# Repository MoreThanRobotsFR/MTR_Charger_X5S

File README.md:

<!-- markdownlint-configure-file { "MD004": { "style": "consistent" } } -->
<!-- markdownlint-disable MD033 -->
<p align="center">
    
    <br>
    <strong>Coding, Hardware and fun !</strong>
</p>
<!-- markdownlint-enable MD033 -->

<body style="background-color:#FFBF00;">
</body>

# MoreThanRobots
* Check the [YOUTUBE-EN-FR](https://www.youtube.com/@morethanrobots) channel.

# Coding
* C/C++
* Python
* MicroPython
* CircuitPython 

# Hardward
* Arduino Uno / Mega / Nano
* Raspberry Pi / Pico / RP2040
* NodeMCU ESP8266 / ESP32

# Schematic
* Kicad
* Altium designer

# Last Project
* [MTR Reflow Plate](https://github.com/MoreThanRobotsFR/MTR_Reflow_Plate)
* [MTR Tiny MD](https://github.com/MoreThanRobotsFR/MTR_Tiny_MD)
* [MTR Multisensor](https://github.com/MoreThanRobotsFR/MTR_C3_TempHum)

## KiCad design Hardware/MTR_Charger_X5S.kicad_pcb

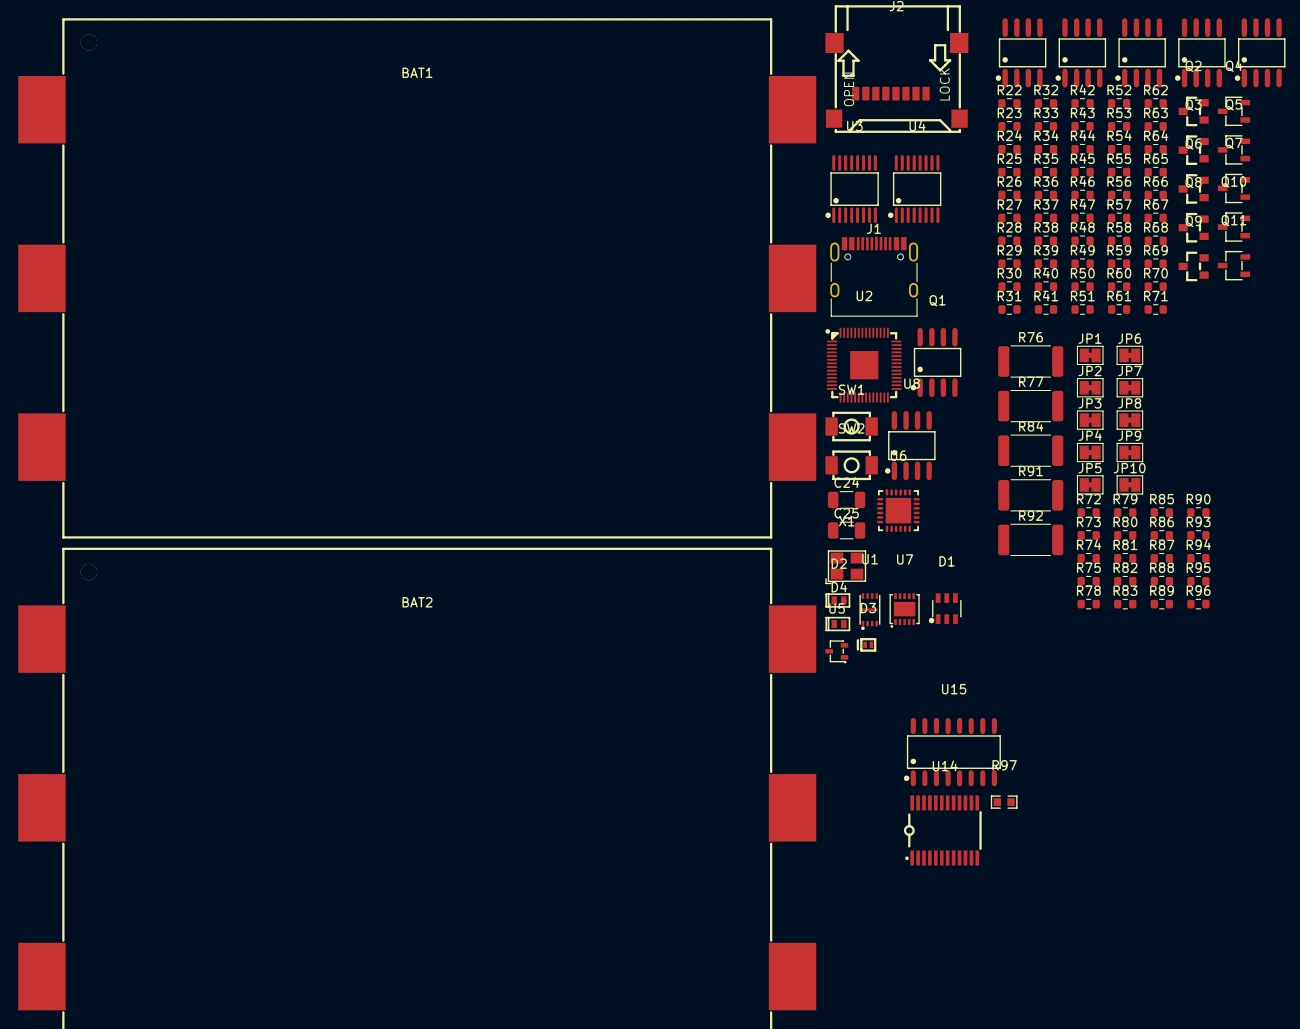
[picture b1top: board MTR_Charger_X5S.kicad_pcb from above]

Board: 2 copper layers, 125 parts (0 on the bottom side), 118 nets, no tracks yet.

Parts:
BAT1, BAT2: BH-18650-B5BA016; BAT-SMD_BH-18650-B5BA016
C24, C25: 1uF; C_1206_3216Metric
D1: USBLC6-2SC6; SOT-23-6_L2.9-W1.6-P0.95-LS2.8-BL
D2, D4: ESDA25P35; DFN1610-2_L1.6-W1.0-P1.05-RD
D3: D_Schottky_Small; X2-DFN1006-2_L1.0-W0.6-P0.65-RD
J1: Korean Hroparts Elec TYPE-C-31-M-12; USB_C_Receptacle_HRO_TYPE-C-31-M-12
J2: Micro_SD_Card; TF-SMD_TF-04A
JP1, JP2, JP3, JP4, JP5, JP6, JP7, JP8, JP9, JP10: SolderJumper_2_Bridged; SolderJumper-2_P1.3mm_Bridged_Pad1.0x1.5mm
Q1: IRF7324TRPBF; SOIC-8_L4.9-W3.9-P1.27-LS6.0-BL
Q2, Q3, Q6, Q8, Q9: AO3401A; SOT-23_L2.9-W1.3-P1.90-LS2.4-BR
Q4, Q5, Q7, Q10, Q11: AO3480C; SOT-23-3_L2.9-W1.6-P1.90-LS2.8-BR
R22, R23, R24, R25, R26, R27, R28, R29, R30, R31, R32, R33, R34, R35, R36, R37, R38, R39, R40, R41, R42, R43, R44, R45, R46, R47, R48, R49, R50, R51, R52, R53, R54, R55, R56, R57, R58, R59, R60, R61, R62, R63, R64, R65, R66, R67, R68, R69, R70, R71, R72, R73, R80, R81, R82, R86, R87, R88, R95, R96: 100k; R_0603_1608Metric
R74, R75, R78, R79, R83, R85, R89, R90, R93, R94: 1k; R_0603_1608Metric
R76, R77, R84, R91, R92: 33m; R_2512_6332Metric
R97: NCP18XH103F03RB; R0603
SW1: Boot; SW-SMD_L4.0-W3.0-LS5.0
SW2: Reset; SW-SMD_L4.0-W3.0-LS5.0
U1: W25Q16JVUXIQ; USON-8_L3.0-W2.0-P0.50-BL-EP
U2: RP2040; LQFN-56_L7.0-W7.0-P0.4-EP
U3, U4: ADS7830IPWR; TSSOP-16_L5.0-W4.4-P0.65-LS6.4-BL
U5: ESDA25W; SOT-323-3_L2.1-W1.3-P1.32-LS2.1-BR
U6: STUSB4500QTR; QFN-24_L4.0-W4.0-P0.50-BL-EP2.8
U7: MCP73833-AMI/MF; DFN-10_L3.0-W3.0-P0.50-BL-EP-1
U8: LMV358IDR; SOIC-8_L4.9-W3.9-P1.27-LS6.0-BL
U9, U10, U11, U12, U13: LMC6482AIMX/NOPB; SOIC-8_L4.9-W3.9-P1.27-LS6.0-BL
U14: TCA9535PWR_C130204; TSSOP-24_L7.8-W4.4-P0.65-LS6.4-BL
U15: CD74HCT4051M96; SOP-16_L10.0-W3.9-P1.27-LS6.0-BL
X1: X322512MSB4SI; OSC-SMD_4P-L3.2-W2.5-BL

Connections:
+1V1: U2.23 (DVDD), U2.45 (VREG_VOUT), U2.50 (DVDD)
+3.3V: U1.8 (VCC), U2.1 (IOVDD), U2.10 (IOVDD), U2.22 (IOVDD), U2.33 (IOVDD), U2.42 (IOVDD), U2.43 (ADC_AVDD), U2.44 (VREG_IN), U2.48 (USB_VDD), U2.49 (IOVDD), U3.16 (+VDD), U4.16 (+VDD), U15.16 (VCC)
+5V: U9.8 (VCC+), U10.8 (VCC+), U11.8 (VCC+), U12.8 (VCC+), U13.8 (VCC+)
/Batteries current sensing/sence_01+: JP1.1 (A), R74.1, R76.1
/Batteries current sensing/sence_01-: JP3.1 (A), R76.2, R78.1
/Batteries current sensing/sence_02+: JP2.1 (A), R75.1, R77.1
/Batteries current sensing/sence_02-: JP4.1 (A), R77.2, R79.1
/Batteries current sensing/sence_03+: JP5.1 (A), R83.1, R84.1
/Batteries current sensing/sence_03-: JP6.1 (A), R84.2, R85.1
/Batteries current sensing/sence_04+: JP7.1 (A), R89.1, R91.1
/Batteries current sensing/sence_04-: JP9.1 (A), R91.2, R93.1
/Batteries current sensing/sence_05+: JP8.1 (A), R90.1, R92.1
/Batteries current sensing/sence_05-: JP10.1 (A), R92.2, R94.1
/CC1: J1.A5 (CC1), U5.1 (K), U6.1 (CC1DB), U6.2 (CC1)
/CC2: J1.B5 (CC2), U5.2 (K), U6.4 (CC2), U6.5 (CC2DB)
/D+: D1.3 (L2), J1.A6 (D+), J1.B6 (D+)
/D-: D1.1 (L1), J1.A7 (D-), J1.B7 (D-)
/Mux_CELL_01_S0: U14.9 (P05), U15.11 (S0)
/Mux_CELL_01_S1: U14.8 (P04), U15.10 (S1)
/Mux_CELL_01_S2: U14.7 (P03), U15.9 (S2)
/PG_Cell_01: U7.7 (~PG), U14.4 (P00)
/PROG_CELL_01: U7.6 (PROG), U15.3 (A)
/STAT1_Cell_01: U7.3 (STAT1), U14.6 (P02)
/STAT2_Cell_01: U7.4 (STAT2), U14.5 (P01)
/XIN: U2.20 (XIN), X1.3
/XOUT: U2.21 (XOUT), X1.1
ALERT: U2.8 (GPIO6), U6.19 (ALERT)
CELL_01+: BAT1.2, JP3.2 (B), Q2.2 (S), R27.2
CELL_02+: BAT1.4, JP4.2 (B), Q3.2 (S), R29.2
CELL_03+: BAT1.6, JP6.2 (B), Q6.2 (S), R45.2
CELL_04+: BAT2.2, JP9.2 (B), Q9.2 (S), R60.2
CELL_05+: BAT2.4, JP10.2 (B), Q8.2 (S), R57.2
CHARGING_01: C25.1, JP1.2 (B), U7.9 (VBAT), U7.10 (VBAT)
Current_cell_01: R80.2, U4.1 (CH0), U9.1
Current_cell_02: R81.2, U4.2 (CH1), U10.1
Current_cell_03: R86.2, U4.3 (CH2), U11.1
Current_cell_04: R95.2, U4.4 (CH3), U12.1
Current_cell_05: R96.2, U4.5 (CH4), U13.1
GND: C24.2, C25.2, D1.2 (VN), D2.2 (A2), D4.2 (A2), J1.A1 (GND), J1.A12 (GND), J1.B1 (GND), J1.B12 (GND), J1.S1 (SHIELD), R22.1, R23.1, R42.1, R52.1, R54.1, R72.2, R73.2, R82.2, R87.2, R88.2, R97.1, SW1.1, SW2.1, U1.4 (GND), U2.19 (TESTEN), U2.57 (GND), U5.3 (A), U6.3 (NC), U6.10 (GND), U6.22 (VSYS), U6.25 (EP), U7.5 (VSS), U7.11 (PAD), U9.4 (GND), U10.4 (GND), U11.4 (GND), U12.4 (GND), U13.4 (GND), U14.12 (GND), U15.6 (~E), U15.7 (VEE), U15.8 (GND), X1.2, X1.4
unnamed: D1.5 (VP), D2.1 (A1), D3.2 (A), J1.A4 (VBUS), J1.A9 (VBUS), J1.B4 (VBUS), J1.B9 (VBUS), Q1.7 (D1), Q1.8 (D1)
unnamed: Q1.2 (G1), Q1.4 (G2)
unnamed: Q1.1 (S1), Q1.3 (S2), U6.24 (VDD)
unnamed: Q2.3 (D), R38.2
unnamed: Q2.1 (G), Q4.3 (D), R27.1
unnamed: Q3.3 (D), R39.2
unnamed: Q3.1 (G), Q5.3 (D), R29.1
unnamed: Q4.2 (S), R40.1
unnamed: Q5.2 (S), R41.1
unnamed: Q6.3 (D), R50.2
unnamed: Q6.1 (G), Q7.3 (D), R45.1
unnamed: Q7.2 (S), R51.1
unnamed: Q8.3 (D), R67.2
unnamed: Q9.3 (D), R69.2
unnamed: Q8.1 (G), Q10.3 (D), R57.1
unnamed: Q10.2 (S), R70.1
unnamed: Q9.1 (G), Q11.3 (D), R60.1
unnamed: Q11.2 (S), R71.1
unnamed: R22.2, R24.1
unnamed: R23.2, R25.1
unnamed: R24.2, R26.2
unnamed: R25.2, R28.2
unnamed: R26.1, R30.1
unnamed: R28.1, R31.1
unnamed: R30.2, R32.1
unnamed: R31.2, R33.1
unnamed: R32.2, R34.2
unnamed: R33.2, R35.2
unnamed: R34.1, R36.1
unnamed: R35.1, R37.1
unnamed: R36.2, R38.1, R40.2, U9.5
unnamed: R37.2, R39.1, R41.2, U10.5
unnamed: R42.2, R43.1
unnamed: R43.2, R44.2
unnamed: R44.1, R46.1
unnamed: R46.2, R47.1
unnamed: R47.2, R48.2
unnamed: R48.1, R49.1
unnamed: R49.2, R50.1, R51.2, U11.5
unnamed: R52.2, R53.1
unnamed: R53.2, R56.2
unnamed: R54.2, R55.1
unnamed: R55.2, R59.2
unnamed: R56.1, R58.1
unnamed: R58.2, R61.1
unnamed: R59.1, R62.1
unnamed: R61.2, R64.2
unnamed: R62.2, R63.1
unnamed: R63.2, R66.2
unnamed: R64.1, R65.1
unnamed: R65.2, R67.1, R70.2, U12.5
unnamed: R66.1, R68.1
unnamed: R68.2, R69.1, R71.2, U13.5
unnamed: R72.1, R74.2, U9.3
unnamed: R73.1, R75.2, U10.3
unnamed: R78.2, R80.1, U9.2
unnamed: R79.2, R81.1, U10.2
unnamed: R82.1, R83.2, U11.3
unnamed: R85.2, R86.1, U11.2
unnamed: R87.1, R89.2, U12.3
unnamed: R88.1, R90.2, U13.3
unnamed: R93.2, R95.1, U12.2
unnamed: R94.2, R96.1, U13.2
unnamed: R97.2, U7.8 (THERM)
unnamed: U8.1, U8.6
QSPI_CLK: U1.6 (CLK), U2.52 (QSPI_SCLK)
QSPI_SD0: U1.5 (DI(IO0)), U2.53 (QSPI_SD0)
QSPI_SD1: U1.2 (DO(IO1)), U2.55 (QSPI_SD1)
QSPI_SD2: U1.3 (WP#(IO2)), U2.54 (QSPI_SD2)
QSPI_SD3: U1.7 (RESET#(IO3)), U2.51 (QSPI_SD3)
QSPI_SS: U1.1 (~CS), U2.56 (QSPI_SS)
SCL: U2.7 (GPIO5), U3.14 (SCL), U4.14 (SCL), U6.7 (SCL)
SDA: U2.6 (GPIO4), U3.15 (SDA), U4.15 (SDA), U6.8 (SDA)
Voltage_cell_01: U3.1 (CH0), U9.6, U9.7
Voltage_cell_02: U3.2 (CH1), U10.6, U10.7
Voltage_cell_03: U3.3 (CH2), U11.6, U11.7
Voltage_cell_04: U3.4 (CH3), U13.6, U13.7
Voltage_cell_05: U3.5 (CH4), U12.6, U12.7
Vsnk: C24.1, D4.1 (A1), Q1.5 (D2), Q1.6 (D2), U7.1 (VDD), U7.2 (VDD)

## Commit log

2024-06-21 init
2024-06-24 USC C and PD done
2024-06-24 RP2040 and QSPI Flash done
2024-06-24 Current and Voltage sensing done
2024-06-28 Add Mux for Battery charging current selection
2024-07-02 Add platformIO
2024-07-02 Add firmware
2024-07-02 chore: Update MTR_STUSB4500 subproject commit to a5452fb11d53842c4aa69bf212f6313601b2d151-dirty
2024-07-06 Add battery ic
